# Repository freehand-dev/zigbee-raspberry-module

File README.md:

# cc2538-raspberry-pi-module

> ZigBee CC2538 Raspberry Pi module + RTC

## PCB 3D images

## Firmware
> You could flash the firmware by JTAG programmer or directly from the Raspberry Pi using [cc2538-prog](https://github.com/1248/cc2538-prog/). You have to flash a firmware with a serial bootloader (SBL).

<b>JTAG</b>
in progress

<b>Raspberry Pi (GPIO)</b>
While PowerOn a Raspberry Pi, hold down the `FLASH` button on the shield press `RESET` shortly. The CC2538 now in the bootloader.

Run 

    ./cc2538-prog -d /dev/ttyAMA0 -f MODKAMRU_V3_UART-no-flow-control_with_SBL.hex

Reset the module using the RESET button.

## RTC
Run raspi config on the terminal: 

    sudo raspi-config

- In the configuration tool, select Interfacing Option.
- Then enable I2C by selecting P5 I2C.
- After enabling the I2C.

Reboot the Pi with 

    sudo shutdown -r now

We need to install python-smbus i2c-tools to see whether our Raspberry Pi detected our I2C connection from the RTC module.

    sudo apt-get install python-smbus i2c-tools
    sudo i2cdetect -y 1

With I2C successfully setup and verified that we could see our RTC circuit then we can begin the process of configuring the Raspberry Pi to use our RTC Chip for its time.

Run the following command on your Raspberry PI to begin editing the /boot/config.txt file.

    sudo nano /boot/config.txt

Add line

    dtoverlay=i2c-rtc,ds3231

With that change made we need to restart the Raspberry Pi, so it loads in the latest configuration changes.

    sudo shutdown -r now

Once your Raspberry Pi has finished restarting we can now run the following command, this is so we can make sure that the kernel drivers for the RTC Chip are loaded in

    sudo i2cdetect -y 1

> You should see a wall of text appear, if UU appears instead of 68 then we have successfully loaded in the Kernel driver for our RTC circuit.

Now that we have successfully got the kernel driver activated for the RTC Chip and we know it’s communicating with the Raspberry Pi, we need to remove the fake hwclock package. This package acts as a placeholder for the real hardware clock when you don’t have one.

Type the following two commands into the terminal on your Raspberry Pi to remove the fake-hwclock package. We also remove hwclock from any startup scripts as we will no longer need this.

    sudo apt-get -y remove fake-hwclock
    sudo update-rc.d -f fake-hwclock remove

Now that we have disabled the fake-hwclock package we can proceed with getting the original hardware clock script that is included in Raspbian up and running again by commenting out a section of code.

Run the following command to begin editing the original RTC script.

    sudo nano /lib/udev/hwclock-set

Find and comment out the following three lines by placing # in front of it as we have done below.

    if [ -e /run/systemd/system ] ; then
        exit 0
    fi

<b>Syncing time from the Pi to the RTC module</b>

You can read the time directly from the RTC module by running the following command if you try it now you will notice it is currently way off our current real-time.

    sudo hwclock -D -r

Now before we go ahead and sync the correct time from our Raspberry Pi to our RTC module, we need to run the following command to make sure the time on the Raspberry Pi is in fact correct. If the time is not right, make sure that you are connected to a Wi-Fi or Ethernet connection.

    date

If the time displayed by the date command is correct, we can go ahead and run the following command on your Raspberry Pi. This command will write the time from the Raspberry Pi to the RTC Module.

    sudo hwclock -w

Now if you read the time directly from the RTC module again, you will notice that it has been changed to the same time as what your Raspberry Pi was set at. You should never have to rerun the previous command if you keep a battery in your RTC module.

    sudo hwclock -r

## Bill of Materials
| Name | Designator | Quantity | Footprint | Buy | Description |
|------|------------|----------|-----------|-----|-------------|
| CC2538_CC2592 | U1 | 1 | CC2538-CC2592:CC2538_CC2592 | [aliexpress](https://aliexpress.ru/item/4000955681721.html) | Chinese CC2538_CC2592 zigbee module | 
| DS3231M | U2 | 1 | Package_SO:SOIC-16W_7.5x10.3mm_P1.27mm | [aliexpress](https://aliexpress.ru/item/4000106115557.html) | |
| Conn_01x07 | JTAG1 | 1 | Connector_Harwin:Harwin_M20-89007xx_1x07_P2.54mm_Horizontal | [aliexpress](https://aliexpress.ru/item/32821748577.html) | |
| Conn_02x05 | J1 | 1 |Connector_PinSocket_2.54mm:PinSocket_2x05_P2.54mm_Vertical | [aliexpress](https://aliexpress.ru/item/33004522737.html) | | 
| BK-870 | J2 | 1 | MPD_BK-870 | [aliexpress](https://aliexpress.ru/item/33014348787.html) | |
| B3U-1000P | SW1, SW2 | 2 | Button_Switch_SMD:SW_SPST_B3U-1000P | [aliexpress](https://aliexpress.ru/item/32623923874.html) | | 
| 1k | R1| 1 | Resistor_SMD:R_0805_2012Metric | | |
| 10k | R2, R3, R4 | 3 | Resistor_SMD:R_0805_2012Metric | | | 
| 33uF | C1 | 1 | Capacitor_Tantalum_SMD:CP_EIA-3216-18_Kemet-A | [aliexpress](https://aliexpress.ru/item/4001241518347.html) | A 10V33UF 336 | 
| IPEX_RP-SMA-K | | 1 | | [aliexpress](https://aliexpress.ru/item/10000000385894.html) | SMA Female |

## Links
* Z-Stack Firmware - https://github.com/Koenkk/Z-Stack-firmware
* UART Version of the Z-Stack firmware - https://github.com/reverieline/CC2538-CC2592-ZNP/tree/master/MODKAMRU_V3
* Kicad symbol, footprint, 3D model for CC2538-CC2592 Zigbee RF module. - https://github.com/uzsito/CC2538-CC2592-kicad-component
* Programmer for CC2538 backdoor UART bootloader - https://github.com/1248/cc2538-prog/
* Raspberry Pi UART configuration - https://www.raspberrypi.org/documentation/configuration/uart.md

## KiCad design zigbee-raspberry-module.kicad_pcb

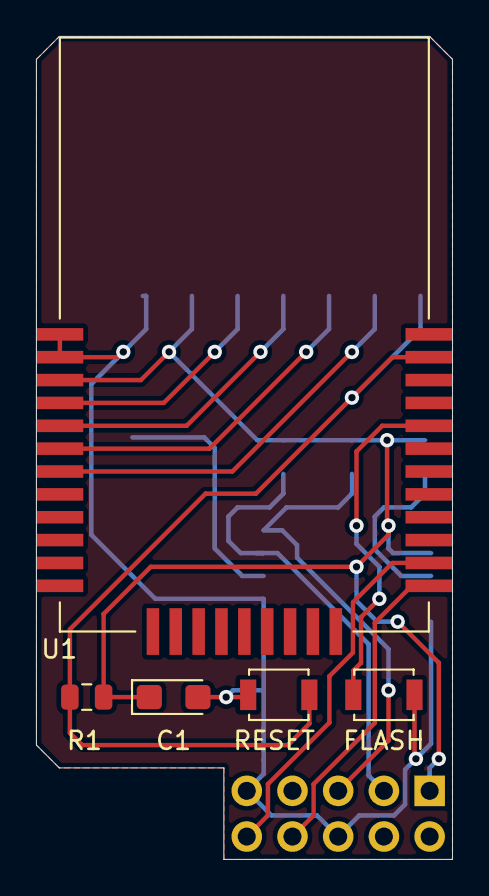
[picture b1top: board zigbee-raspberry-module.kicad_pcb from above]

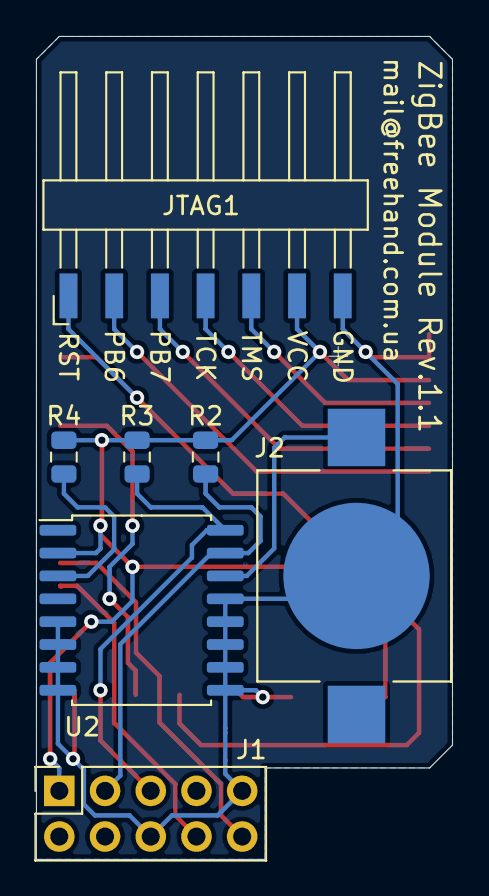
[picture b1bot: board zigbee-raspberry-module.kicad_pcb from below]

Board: 2 copper layers, 23.1 x 45.7 mm, 12 parts (7 on the bottom side), 14 nets.

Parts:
C1: 33uF; CP_EIA-3216-18_Kemet-A
FLASH: FLASH; SW_SPST_B3U-1000P
J1: Conn_02x05_Odd_Even; PinSocket_2x05_P2.54mm_Vertical
J2: BK-870; MPD_BK-870
JTAG1: Conn_01x07; Harwin_M20-89007xx_1x07_P2.54mm_Horizontal
R1: 1k; R_0805_2012Metric
R2, R3, R4: 10k; R_0805_2012Metric
RESET: RESET; SW_SPST_B3U-1000P
U1: CC2538_CC2592
U2: DS3231M; SOIC-16W_7.5x10.3mm_P1.27mm

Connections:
GND: C1.2, FLASH.2, J1.6, J1.9, J2.2, JTAG1.7, RESET.2, U1.1, U1.2, U2.5, U2.6, U2.7, U2.8, U2.9, U2.10, U2.11, U2.12, U2.13
unnamed: J2.1, U2.14
unnamed: R4.2, U2.3
unnamed: FLASH.1, U1.29
PB6: JTAG1.2, U1.7
PB7: JTAG1.3, U1.6
RST: JTAG1.1, R1.1, RESET.1, U1.32
RXD: J1.8, U1.22
SCL: J1.5, R3.2, U2.16
SDA: J1.3, R2.2, U2.15
TCK: JTAG1.4, U1.5
TMS: JTAG1.5, U1.4
TXD: J1.10, U1.23
VCC: C1.1, J1.1, JTAG1.6, R1.2, R2.1, R3.1, R4.1, U1.3, U2.2

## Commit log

2020-11-15 revision 1.1
2020-12-14 uart conf
